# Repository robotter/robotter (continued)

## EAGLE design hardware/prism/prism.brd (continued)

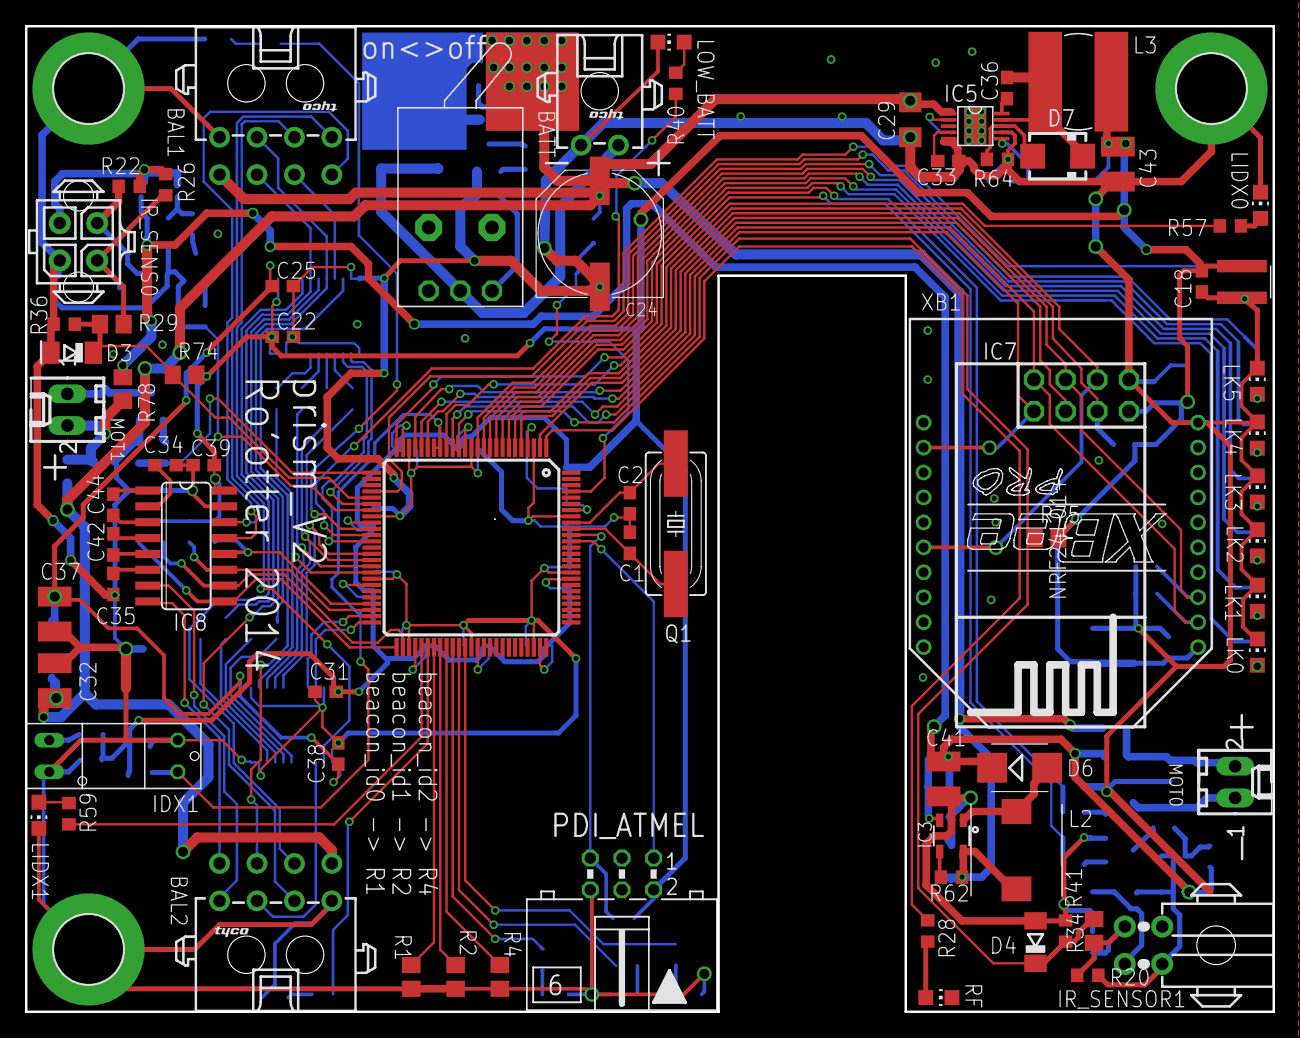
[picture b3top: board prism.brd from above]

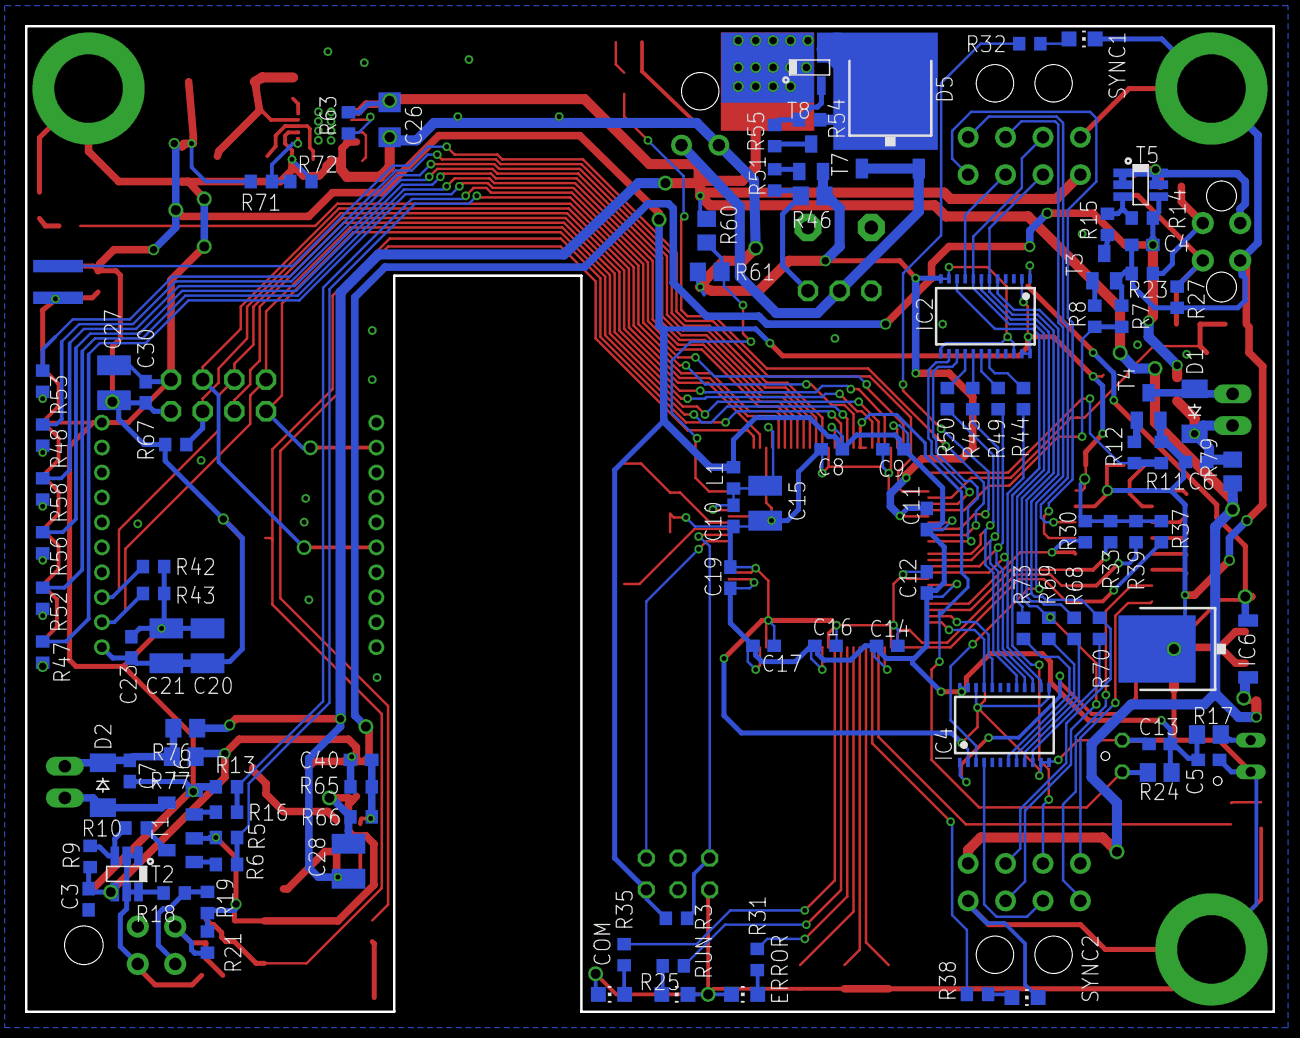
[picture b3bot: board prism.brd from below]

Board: 2 copper layers, 100.0 x 79.0 mm, 180 parts (104 on the bottom side), 130 nets.

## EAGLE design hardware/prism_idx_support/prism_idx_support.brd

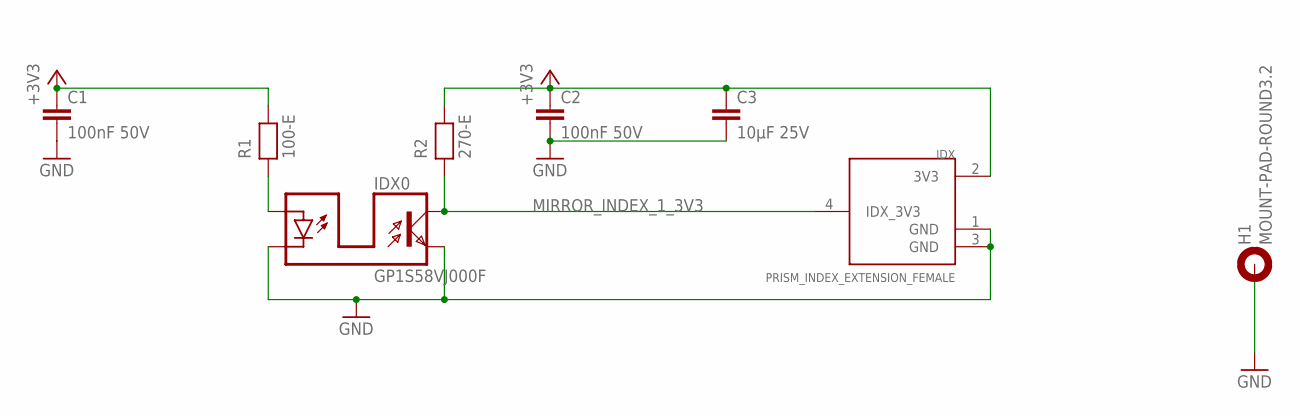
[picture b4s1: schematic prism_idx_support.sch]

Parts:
C1, C2: 100nF 50V; C0603
C3: 10µF 25V; C1210
H1: MOUNT-PAD-ROUND3.2; 3,2-PAD
IDX: PRISM_INDEX_EXTENSION_FEMALE
IDX0: GP1S58VJ000F
R1: 100-E; R0805
R2: 270-E; R0805

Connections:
+3V3: C1.1, C2.1, C3.1, IDX.2 (3V3), R1.2, R2.2
GND: C1.2, C2.2, C3.2, H1.B3,2, IDX.1 (GND), IDX.3 (GND), IDX0.LED_C, IDX0.TRANSISTOR_E
MIRROR_INDEX_1_3V3: IDX.4 (IDX_3V3), IDX0.TRANSISTOR_C, R2.1
unnamed: IDX0.LED_A, R1.1

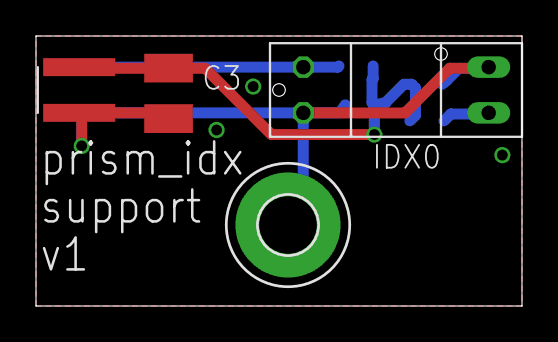
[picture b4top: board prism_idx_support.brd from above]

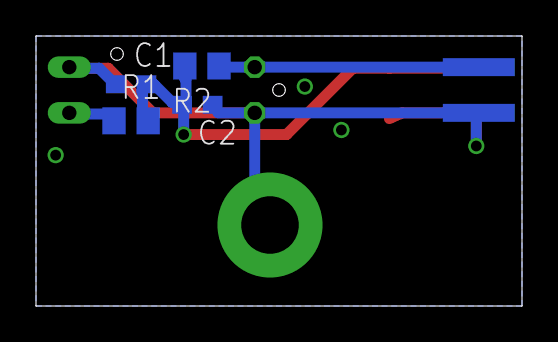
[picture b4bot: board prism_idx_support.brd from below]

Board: 2 copper layers, 27.0 x 15.0 mm, 8 parts (4 on the bottom side), 4 nets.
